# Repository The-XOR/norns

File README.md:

# Trapanaorecchie
Versione vergognosa e barbona dello stilosissimo monome norns.

Funzionante e compatibile al 100%, con vere porte MIDI e un uscita cuffia che non esitiamo a definire "molto utile".

L'aspetto l'e' quel che l'e', ma fatto com'e' con tutti pezzi di recupero, di piu' non si poteva fare.

## quick reference

```
git clone https://github.com/The-XOR/norns.git
cd norns
git submodule update --init --recursive
./waf configure --release
./waf build --release
```

(NB: the `--release` flag creates builds specifically for armv8/cortex-a53 instruction set, meaning optimized for rpi3 and compatible with rpi4. It also enables aggressive compiler optimizations. Omit flag if you need debug symbols or to build for a different architecture. It does need to supplied to both configuration and build steps.)

## documentation
- [user docs](https://monome.org/docs/norns)
- [API docs](https://monome.org/docs/norns/api)
- [building and execution](readme-setup.md)
- [discussion and help](https://llllllll.co)

## related
### supporting repositories
- [maiden](https://github.com/The-XOR/maiden/) | editing interface
- [softcut](https://github.com/monome/softcut-lib) | sample-cutting editor part of `matron`

### tools
- [norns disk image](https://github.com/The-XOR/norns-image) | raspbian-based disk image
- [monome linux kernel](https://github.com/monome/linux/) | custom, monome-flavored linux kernel
- [DIY shield instructions](https://github.com/monome/norns-shield) | the DIY open-source hardware variant

## acknowledgments

`matron` (control system) and `crone` (audio system) were created by [@catfact](https://github.com/catfact). `maiden` (editor) was created by [@ngwese](https://github.com/ngwese). Each grew with contributions from [@artfwo](https://github.com/artfwo), [@antonhornquist](https://github.com/antonhornquist), [@simonvanderveldt](https://github.com/simonvanderveldt),[@ranch-verdin](https://github.com/ranch-verdin), [@pq](https://github.com/pq), [@markwheeler](https://github.com/markwheeler), [@csboling](https://github.com/csboling) and many others.

norns was initiated by [@tehn](https://github.com/tehn) (monome).

## la fotogalleria...

... che lo mostra in tutto il suo splendore. Il colore e' quello pentecostale, a ricordare le ristrettezze economiche che hanno dato i natali.

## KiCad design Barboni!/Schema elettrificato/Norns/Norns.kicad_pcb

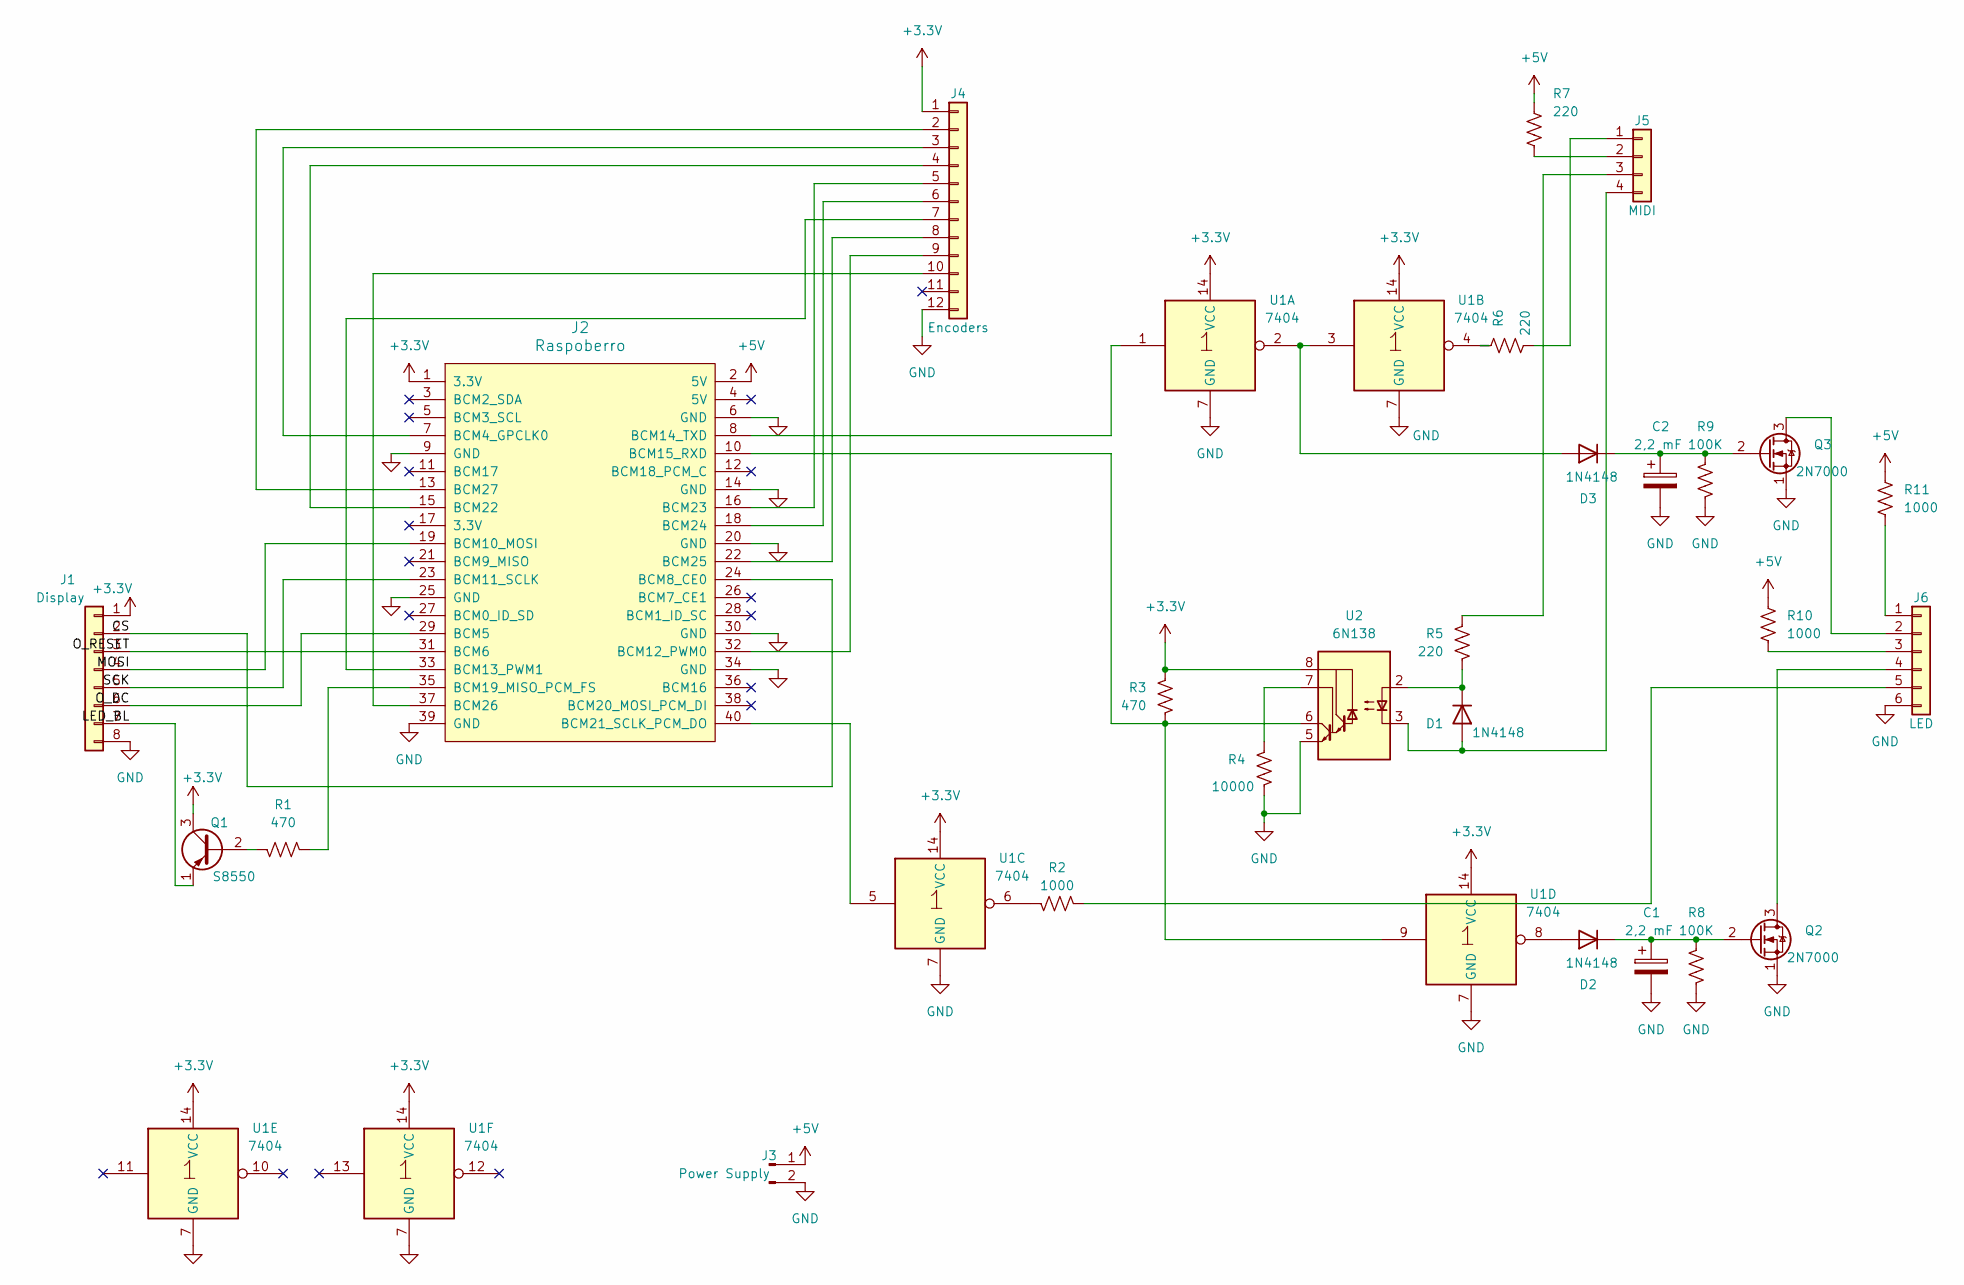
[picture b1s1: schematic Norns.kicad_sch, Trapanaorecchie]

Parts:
C1, C2: 2,2 mF; CP_Radial_D5.0mm_P2.50mm
D1, D2, D3: 1N4148; D_DO-35_SOD27_P7.62mm_Horizontal
J1: Display; JST_EH_B8B-EH-A_1x08_P2.50mm_Vertical
J2: Raspoberro; RPI_Hat_B+_No_Camera
J3: Power Supply; JST_EH_B2B-EH-A_1x02_P2.50mm_Vertical
J4: Encoders; JST_EH_B12B-EH-A_1x12_P2.50mm_Vertical
J5: MIDI; JST_EH_B4B-EH-A_1x04_P2.50mm_Vertical
J6: LED; JST_EH_B6B-EH-A_1x06_P2.50mm_Vertical
Q1: S8550; TO-92_Inline
Q2, Q3: 2N7000; TO-92_Inline
R1, R3: 470; R_Axial_DIN0204_L3.6mm_D1.6mm_P5.08mm_Horizontal
R2, R10, R11: 1000; R_Axial_DIN0204_L3.6mm_D1.6mm_P5.08mm_Horizontal
R4: 10000; R_Axial_DIN0204_L3.6mm_D1.6mm_P5.08mm_Horizontal
R5, R6, R7: 220; R_Axial_DIN0204_L3.6mm_D1.6mm_P5.08mm_Horizontal
R8, R9: 100K; R_Axial_DIN0204_L3.6mm_D1.6mm_P5.08mm_Horizontal
U1: 7404; DIP-14_W7.62mm
U2: 6N138; DIP-8_W7.62mm

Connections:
+3.3V: J1.1, J2.1 (3.3V), J4.1, Q1.3 (C), R3.1, U1.14 (VCC), U2.8 (VCC)
+5V: J2.2 (5V), J3.1, R7.2, R10.2, R11.2
/CS: J1.2, J2.24 (BCM8_CE0)
/LED_BL: J1.7, Q1.1 (E)
/MOSI: J1.4, J2.19 (BCM10_MOSI)
/O_DC: J1.6, J2.29 (BCM5)
/O_RESET: J1.3, J2.31 (BCM6)
/SCK: J1.5, J2.23 (BCM11_SCLK)
GND: C1.2, C2.2, J1.8, J2.6 (GND), J2.9 (GND), J2.14 (GND), J2.20 (GND), J2.25 (GND), J2.30 (GND), J2.34 (GND), J2.39 (GND), J3.2, J4.12, J6.6, Q2.1 (S), Q3.1 (S), R4.2, R8.1, R9.1, U1.7 (GND), U2.5 (GND)
unnamed: D1.2 (A), J5.4, U2.3 (C2)
unnamed: D1.1 (K), R5.1, U2.2 (C1)
unnamed: D2.2 (A), U1.8
unnamed: C1.1, D2.1 (K), Q2.2 (G), R8.2
unnamed: D3.2 (A), U1.2, U1.3
unnamed: C2.1, D3.1 (K), Q3.2 (G), R9.2
unnamed: J2.7 (BCM4_GPCLK0), J4.3
unnamed: J2.32 (BCM12_PWM0), J4.9
unnamed: J2.33 (BCM13_PWM1), J4.7
unnamed: J2.8 (BCM14_TXD), U1.1
unnamed: J2.10 (BCM15_RXD), R3.2, U1.9, U2.6 (VO2)
unnamed: J2.35 (BCM19_MISO_PCM_FS), R1.1
unnamed: J2.40 (BCM21_SCLK_PCM_DO), U1.5
unnamed: J2.15 (BCM22), J4.4
unnamed: J2.16 (BCM23), J4.5
unnamed: J2.18 (BCM24), J4.6
unnamed: J2.22 (BCM25), J4.8
unnamed: J2.37 (BCM26), J4.10
unnamed: J2.13 (BCM27), J4.2
unnamed: J5.1, R6.2
unnamed: J5.2, R7.1
unnamed: J5.3, R5.2
unnamed: J6.1, R11.1
unnamed: J6.2, Q3.3 (D)
unnamed: J6.3, R10.1
unnamed: J6.4, Q2.3 (D)
unnamed: J6.5, R2.1
unnamed: Q1.2 (B), R1.2
unnamed: R2.2, U1.6
unnamed: R6.1, U1.4
unnamed: R4.1, U2.7 (VO1)

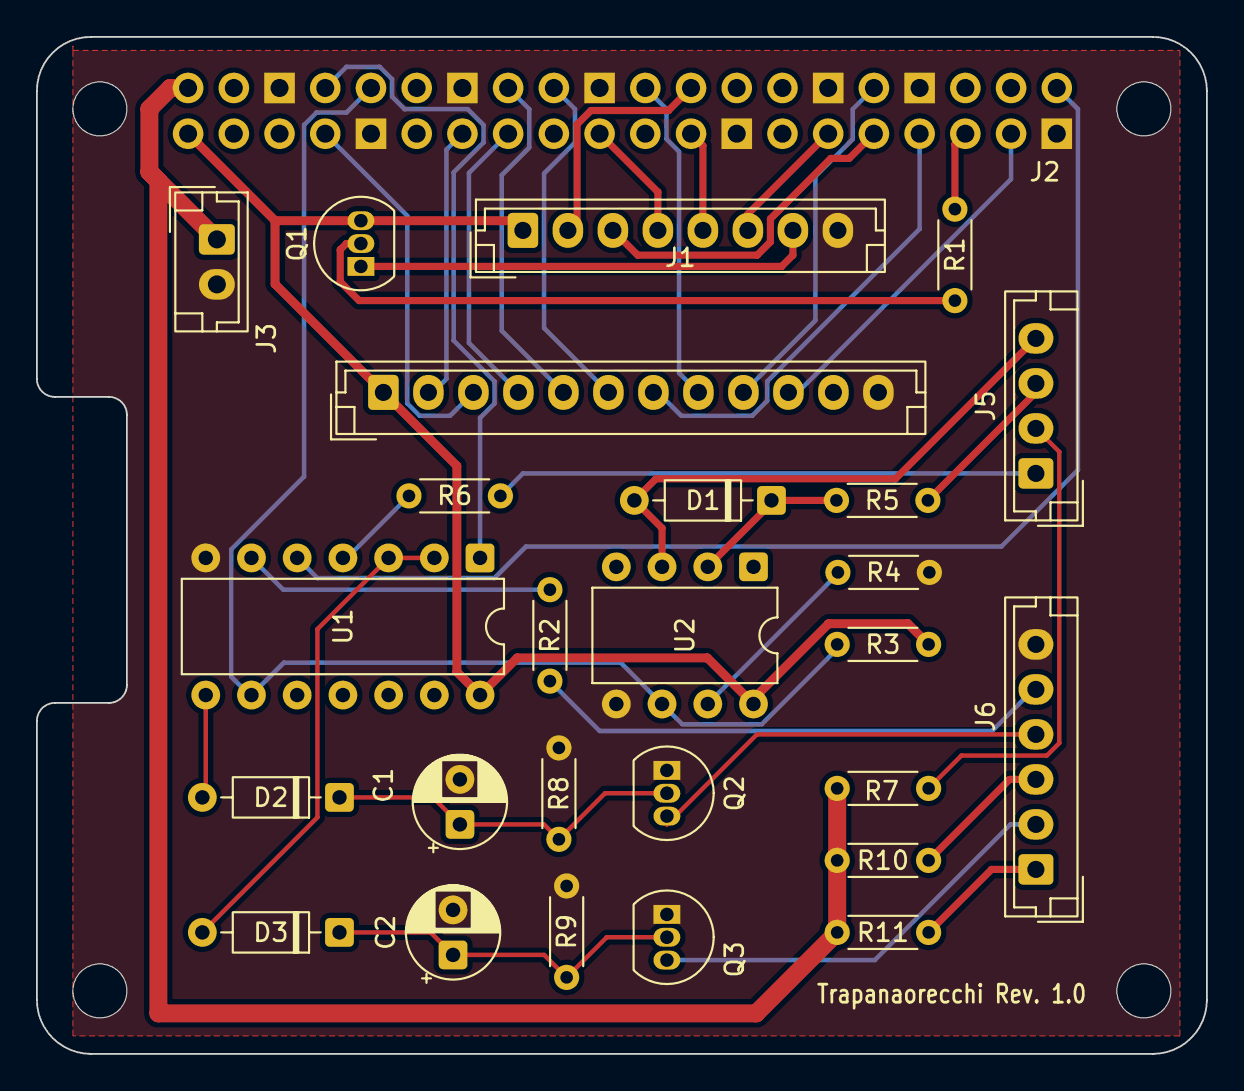
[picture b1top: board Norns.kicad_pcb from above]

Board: 2 copper layers, 65.0 x 56.5 mm, 27 parts (0 on the bottom side), 40 nets.

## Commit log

2020-12-11 push2 enabled
2020-12-13 part uan
2020-12-13 ladies and gentlemen...
2021-02-16 update phase
2021-03-06 segmentation fault fix
2021-07-10 il norns dei barboni
2021-07-11 pinout
2021-07-11 tassonomie
2021-07-18 finito
2021-07-18 FULL COLOR
2021-07-23 pi 4
2022-01-23 sclang
2022-01-25 yeye
2024-12-16 Enhance screen rendering by applying device scaling to surfaces
2024-12-16 CODEC
2024-12-18 img-driven
2024-12-19 maledetto
2024-12-19 clerus
2024-12-19 pesci
2024-12-20 cul de sac
2024-12-20 st7789
2024-12-23 userman
2024-12-24 my way
2024-12-24 ma che disperazione
2024-12-24 millostonno
2024-12-24 fino qui
2024-12-31 millostonno #1
2024-12-31 millostonno #2
2024-12-31 milestonno #3
2024-12-31 schermo funzionante
2024-12-31 migliorie displetiche
2024-12-31 power off mngmnt
2024-12-31 la perfezione dei barboni
2025-01-01 hardware fix
2025-01-02 ultii aggiustamenti allo schermo
2025-01-03 vicini alla perfezione
2025-01-03 user manual
2025-01-04 copertun
2025-01-07 barbonate varie
2025-01-18 lcd a 3.3V
2025-03-16 grande zia assunta!
2025-03-20 pinouts
2025-04-02 potenziometro antilogaritmico
2025-04-03 potenzometro antilog
2025-05-15 update, non ci siamo ancora
2025-05-15 backlight con transistore piennepi
2025-06-26 tutto funge
2025-06-26 spigolature
2025-10-28 scatulun
2026-01-13 la si avanza
2026-01-16 gerb
2026-01-18 avanzamento di progressione
2026-01-19 schema el
2026-01-22 scatola inf terminata
2026-01-22 quas fernut
2026-01-22 scatola base ok
2026-01-22 scatola terminata
2026-01-22 rimosse vecchie code
2026-01-27 front
2026-01-29 altra iterasiun
2026-01-31 test 2
2026-02-02 scatola2
2026-02-04 ULTIMO
2026-05-28 latest
2026-05-29 modifiche
2026-06-01 foto
2026-06-01 reasdme
2026-06-02 prep
2026-06-05 committamento
2026-06-05 aricommit
